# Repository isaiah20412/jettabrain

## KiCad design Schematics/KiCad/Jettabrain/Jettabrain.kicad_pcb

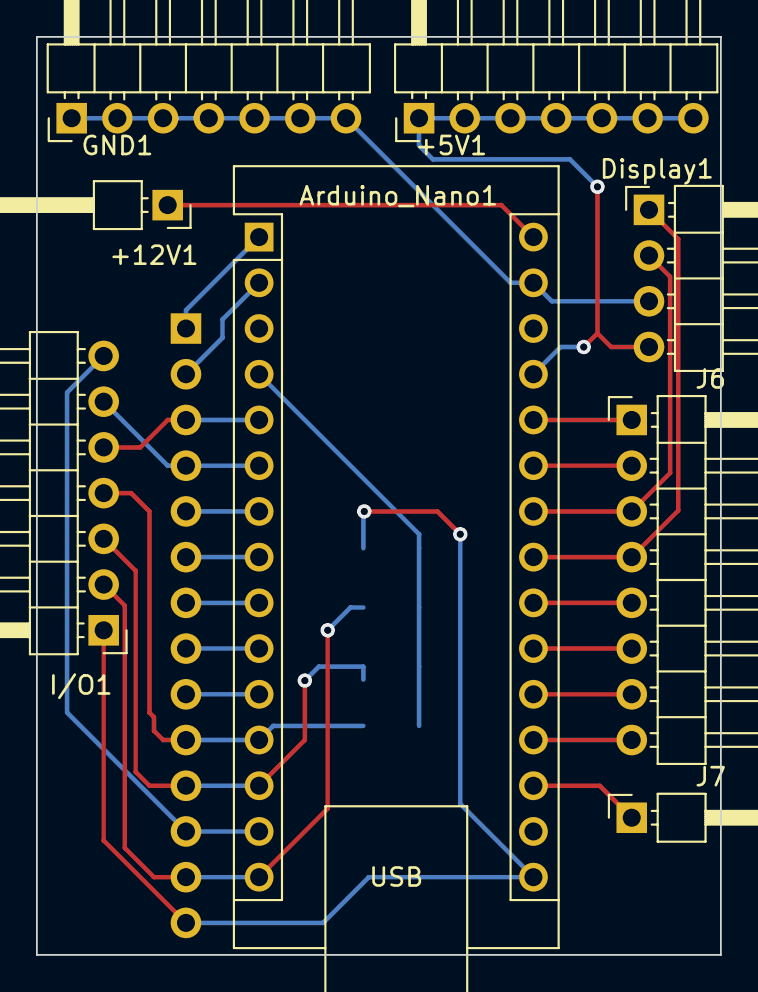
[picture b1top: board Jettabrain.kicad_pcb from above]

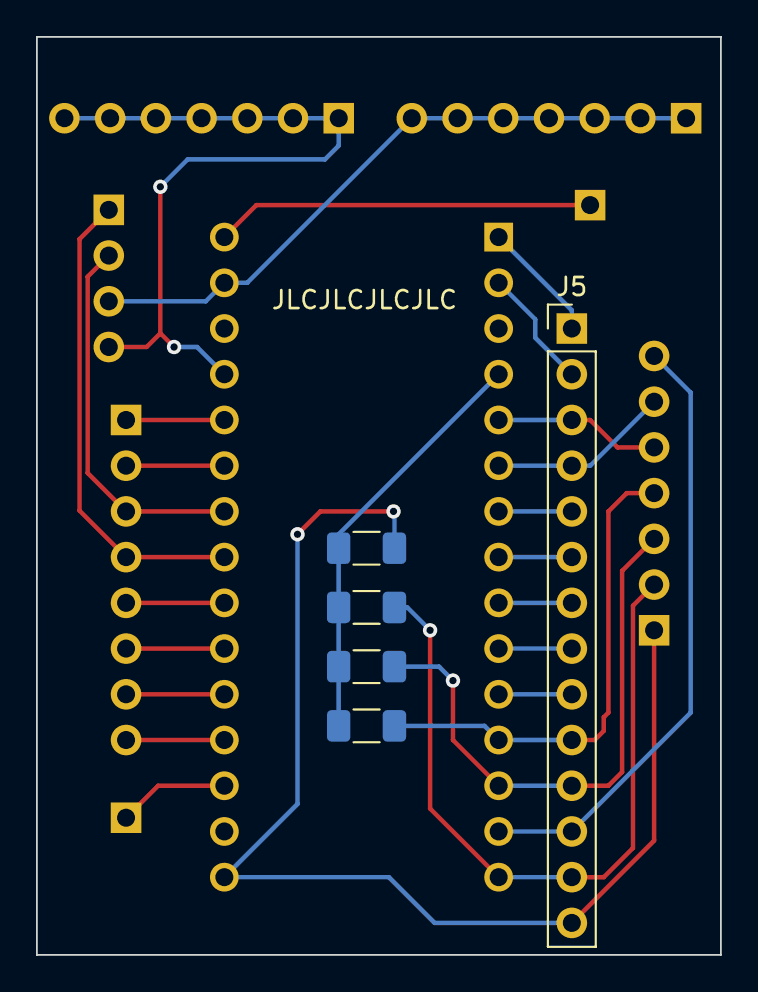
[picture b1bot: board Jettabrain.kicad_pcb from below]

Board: 2 copper layers, 38.0 x 51.0 mm, 13 parts (5 on the bottom side), 27 nets.

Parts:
+5V1: Conn_01x07_Pin; PinHeader_1x07_P2.54mm_Horizontal
+12V1: Conn_01x01_Pin; PinHeader_1x01_P2.54mm_Horizontal
Arduino_Nano1: Arduino_Nano_v3.x; Arduino_Nano
Display1: Conn_01x04; PinHeader_1x04_P2.54mm_Horizontal
GND1: Conn_01x07_Pin; PinHeader_1x07_P2.54mm_Horizontal
I/O1: Conn_01x07_Pin; PinHeader_1x07_P2.54mm_Horizontal
J5: Conn_01x14_Pin; PinHeader_1x14_P2.54mm_Vertical
J6: Conn_01x08_Pin; PinHeader_1x08_P2.54mm_Horizontal
J7: Conn_01x01_Pin; PinHeader_1x01_P2.54mm_Horizontal
R1, R2, R3, R4: 220R; R_1206_3216Metric_Pad1.30x1.75mm_HandSolder

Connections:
GND: Arduino_Nano1.29 (GND), Display1.3, GND1.1, GND1.2, GND1.3, GND1.4, GND1.5, GND1.6, GND1.7
unnamed: +5V1.1, +5V1.2, +5V1.3, +5V1.4, +5V1.5, +5V1.6, +5V1.7, Arduino_Nano1.27 (+5V), Display1.4
unnamed: +12V1.1, Arduino_Nano1.30 (VIN)
unnamed: Arduino_Nano1.19 (A0), J6.8
unnamed: Arduino_Nano1.20 (A1), J6.7
unnamed: Arduino_Nano1.21 (A2), J6.6
unnamed: Arduino_Nano1.22 (A3), J6.5
unnamed: Arduino_Nano1.23 (A4), Display1.1, J6.4
unnamed: Arduino_Nano1.24 (A5), Display1.2, J6.3
unnamed: Arduino_Nano1.25 (A6), J6.2
unnamed: Arduino_Nano1.26 (A7), J6.1
unnamed: Arduino_Nano1.18 (AREF), J7.1
unnamed: Arduino_Nano1.2 (D0/RX), J5.2
unnamed: Arduino_Nano1.1 (D1/TX), J5.1
unnamed: Arduino_Nano1.5 (D2), I/O1.5, J5.3
unnamed: Arduino_Nano1.6 (D3), I/O1.6, J5.4
unnamed: Arduino_Nano1.7 (D4), J5.5
unnamed: Arduino_Nano1.8 (D5), J5.6
unnamed: Arduino_Nano1.9 (D6), J5.7
unnamed: Arduino_Nano1.10 (D7), J5.8
unnamed: Arduino_Nano1.11 (D8), J5.9
unnamed: Arduino_Nano1.12 (D9), I/O1.4, J5.10, R4.2
unnamed: Arduino_Nano1.13 (D10), I/O1.3, J5.11, R3.2
unnamed: Arduino_Nano1.14 (D11), I/O1.7, J5.12
unnamed: Arduino_Nano1.15 (D12), I/O1.2, J5.13, R2.2
unnamed: Arduino_Nano1.16 (D13), I/O1.1, J5.14, R1.2
unnamed: Arduino_Nano1.4 (GND), R1.1, R2.1, R3.1, R4.1

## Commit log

2024-01-06 Initial Commit (Also some schematics)
2024-01-06 Added .gitignore.
2024-01-06 Updated .gitignore.
2024-01-06 Initial sketch setup.
2024-01-06 Main Menu Configuration
2024-01-06 Ibid
2024-01-07 Updates.
2024-01-08 Updated arduino.json File
2024-01-08 Main Code Body Created
2024-01-09 Updated Brights
2024-01-09 New Scematics/PCB Files
2024-01-10 KiCad Schematics and PCB Design
2024-01-10 Cleaned up KiCad Folder
2024-01-10 Generated Gerber Files
2024-01-10 Fixed Relay Pin HIGH/LOWs The relay module used on this project is a bit weird. Writing a LOW signal to a pin causes the relay module to energize its respective coil, thus closing the "NO" relay circ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
2024-01-19 PCB Updates
2024-01-25 Schematic & Code Updates Final pre-production update to the program... Hopefully!
2024-02-02 Removed Auto Function Auto function has been commented/edited out for now due to optocoupler issues. If I ever have time or figure out a better way to do this, I may update the code and bring it back.
2024-02-02 Updated Display Scaling
2024-02-02 Cleaned up Code Cleaned up scrap code/not currently in use. Created a file *[[Code Snippets.md]]* to store snippets that may be useful later.
